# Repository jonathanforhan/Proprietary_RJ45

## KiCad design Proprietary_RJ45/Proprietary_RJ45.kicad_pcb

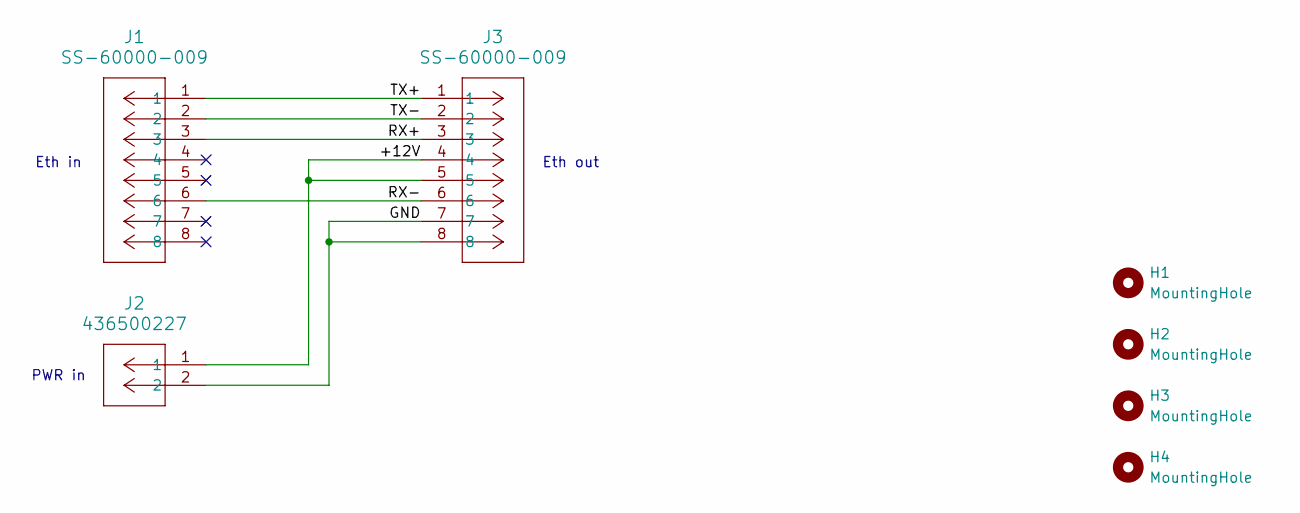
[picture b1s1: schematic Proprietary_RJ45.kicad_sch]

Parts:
H1, H2, H3, H4: MountingHole; MountingHole_2.7mm_M2.5
J1, J3: SS-60000-009; CONN8_SS-60000_STW
J2: 436500227; CONN_SD-43650-010_02_MOL

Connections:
/+12V: J2.1, J3.4, J3.5
/GND: J2.2, J3.7, J3.8
/RX+: J1.3, J3.3
/RX-: J1.6, J3.6
/TX+: J1.1, J3.1
/TX-: J1.2, J3.2

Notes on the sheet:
Eth in
Eth out
PWR in

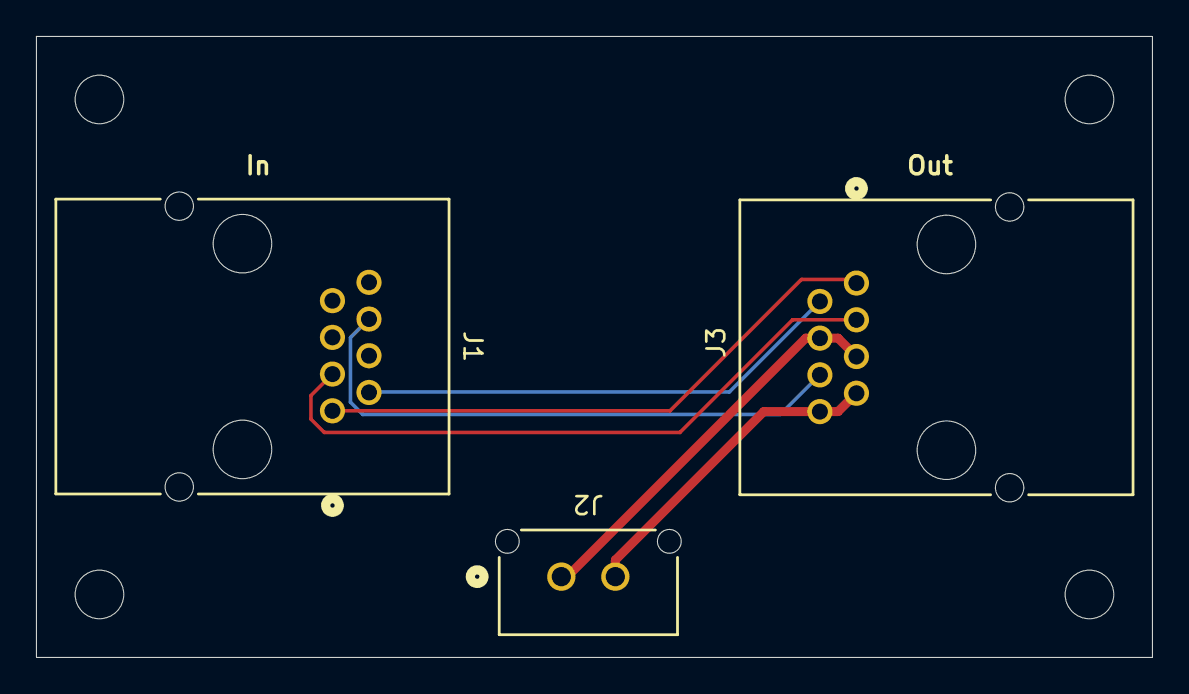
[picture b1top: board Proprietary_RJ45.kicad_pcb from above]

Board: 2 copper layers, 62.0 x 34.5 mm, 7 parts (0 on the bottom side), 6 nets.

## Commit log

2026-01-20 make PWR and GND trace widths larger
2026-02-10 add 3D models to project
2026-02-18 fix line width for DRC check
